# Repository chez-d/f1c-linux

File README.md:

# f1c-linux
This is a little breakout I made for Allwinner's F1C100s/200s a while ago, also known as the "potatoboard" (it's a 533 MHz ARM9 CPU).

This chip is pretty amazing in terms of cost -- for a couple of $$ you can get really impressive performance, at least if you ignore floating point, and up to 64 MB (!!) of DDR as SiP, so no annoying routing to be seen. This board is designed for JLC's low-cost 4 layer boards and you can even get it assembled by them for pretty cheap, go check out the `fab/` folder for the gerbers and POS files!

I used LDOs on this design so I don't have to deal with switching regulator headaches... so not so great power usage.

Upload to the SPI NOR with the USB connector and the handy `sunxi-fel` tool, or you could try and hook up a SD/MMC card on the GPIO. It even runs Linux!

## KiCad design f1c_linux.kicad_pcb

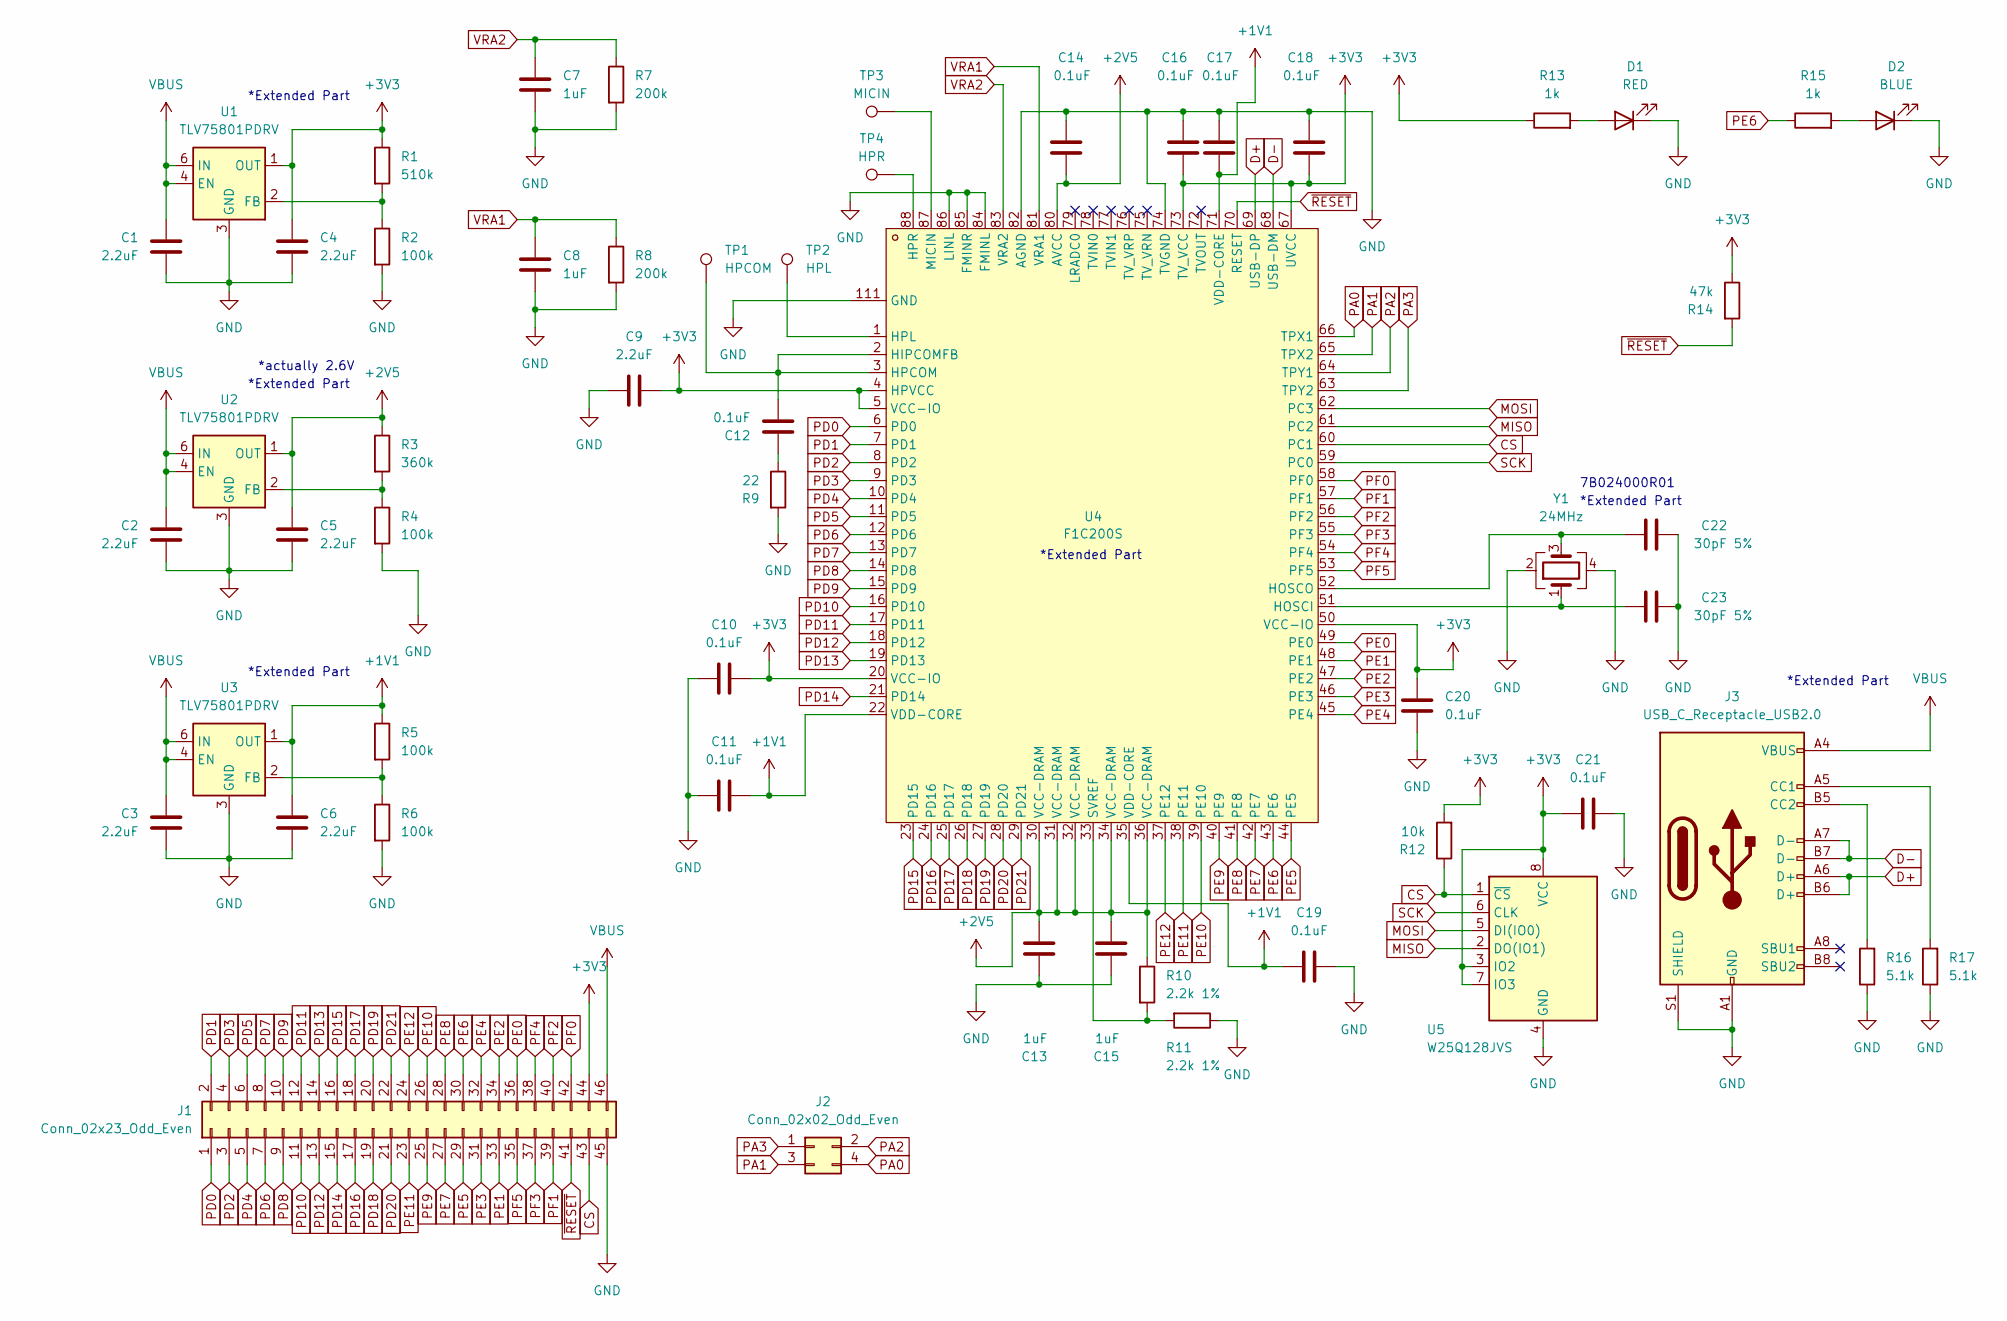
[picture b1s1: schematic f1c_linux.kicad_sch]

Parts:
C1, C2, C3, C4, C5, C6, C9: 2.2uF; C_0603_1608Metric; LCSC Part C23630
C7, C8, C13, C15: 1uF; C_0402_1005Metric; LCSC Part C52923
C10, C11, C12, C14, C16, C17, C18, C19, C20, C21: 0.1uF; C_0402_1005Metric; LCSC Part C307331
C22, C23: 30pF 5%; C_0402_1005Metric; LCSC Part C1570
D1: RED; LED_0603_1608Metric; LCSC Part C2286
D2: BLUE; LED_0603_1608Metric; LCSC Part C72041
J1: Conn_02x23_Odd_Even; PinHeader_2x23_P2.54mm_Vertical
J2: Conn_02x02_Odd_Even; PinHeader_2x02_P2.54mm_Vertical
J3: USB_C_Receptacle_USB2.0; USB_C_Receptacle_G-Switch_GT-USB-7010ASV; LCSC Part C2988369
R1: 510k; R_0402_1005Metric; LCSC Part C11616
R2, R4, R5, R6: 100k; R_0402_1005Metric; LCSC Part C25741
R3: 360k; R_0603_1608Metric; LCSC Part C23146
R7, R8: 200k; R_0402_1005Metric; LCSC Part C25764
R9: 22; R_0402_1005Metric; LCSC Part C25092
R10, R11: 2.2k 1%; R_0402_1005Metric; LCSC Part C25879
R12: 10k; R_0402_1005Metric; LCSC Part C25744
R13, R15: 1k; R_0402_1005Metric; LCSC Part C11702
R14: 47k; R_0402_1005Metric; LCSC Part C25792
R16, R17: 5.1k; R_0402_1005Metric; LCSC Part C25905
TP1: HPCOM; TestPoint_Pad_D2.0mm
TP2: HPL; TestPoint_Pad_D2.0mm
TP3: MICIN; TestPoint_Pad_D2.0mm
TP4: HPR; TestPoint_Pad_D2.0mm
U1, U2, U3: TLV75801PDRV; WSON-6-1EP_2x2mm_P0.65mm_EP1x1.6mm; LCSC Part C2876308
U4: F1C200S; QFN-88_L10.0-W10.0-P0.40-BL-EP6.75; LCSC Part C2879851
U5: W25Q128JVS; SOIC-8_5.23x5.23mm_P1.27mm; LCSC Part C97521
Y1: 24MHz; Crystal_SMD_3225-4Pin_3.2x2.5mm; LCSC Part C654992

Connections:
+1V1: C6.1, C11.2, C17.1, C19.1, R5.1, U3.1 (OUT), U4.22 (VDD-CORE), U4.35 (VDD-CORE), U4.71 (VDD-CORE)
+2V5: C5.1, C13.1, C14.1, C15.1, R3.1, R10.1, U2.1 (OUT), U4.30 (VCC-DRAM), U4.31 (VCC-DRAM), U4.32 (VCC-DRAM), U4.34 (VCC-DRAM), U4.36 (VCC-DRAM), U4.80 (AVCC)
+3V3: C4.1, C9.2, C10.2, C16.1, C18.1, C20.2, C21.2, J1.44, R1.1, R12.2, R13.1, R14.1, U1.1 (OUT), U4.4 (HPVCC), U4.5 (VCC-IO), U4.20 (VCC-IO), U4.50 (VCC-IO), U4.67 (UVCC), U4.73 (TV_VCC), U5.3 (IO2), U5.7 (IO3), U5.8 (VCC)
CS: J1.43, R12.1, U4.60 (PC1), U5.1 (~CS)
D+: J3.A6 (D+), J3.B6 (D+), U4.69 (USB-DP)
D-: J3.A7 (D-), J3.B7 (D-), U4.68 (USB-DM)
GND: C1.2, C2.2, C3.2, C4.2, C5.2, C6.2, C7.2, C8.2, C9.1, C10.1, C11.1, C13.2, C14.2, C15.2, C16.2, C17.2, C18.2, C19.2, C20.1, C21.1, C22.2, C23.2, D1.1 (K), D2.1 (K), J1.45, J3.A1 (GND), J3.A12 (GND), J3.B1 (GND), J3.B12 (GND), J3.S1 (SHIELD), R2.2, R4.2, R6.2, R7.2, R8.2, R9.2, R11.1, R16.1, R17.1, U1.3 (GND), U1.7 (GND), U2.3 (GND), U2.7 (GND), U3.3 (GND), U3.7 (GND), U4.74 (TVGND), U4.82 (AGND), U4.84 (FMINL), U4.85 (FMINR), U4.86 (LINL), U4.111 (GND), U5.4 (GND), Y1.2, Y1.4
MISO: U4.61 (PC2), U5.2 (DO(IO1))
MOSI: U4.62 (PC3), U5.5 (DI(IO0))
unnamed: C12.1, R9.1
unnamed: D1.2 (A), R13.2
unnamed: D2.2 (A), R15.2
unnamed: J3.A5 (CC1), R17.2
unnamed: J3.B5 (CC2), R16.2
unnamed: R1.2, R2.1, U1.2 (FB)
unnamed: R3.2, R4.1, U2.2 (FB)
unnamed: R5.2, R6.1, U3.2 (FB)
unnamed: C12.2, TP1.1, U4.2 (HIPCOMFB), U4.3 (HPCOM)
unnamed: C23.1, U4.51 (HOSCI), Y1.1
unnamed: C22.1, U4.52 (HOSCO), Y1.3
unnamed: TP2.1, U4.1 (HPL)
unnamed: TP4.1, U4.88 (HPR)
unnamed: TP3.1, U4.87 (MICIN)
unnamed: R10.2, R11.2, U4.33 (SVREF)
PA0: J2.4, U4.66 (TPX1)
PA1: J2.3, U4.65 (TPX2)
PA2: J2.2, U4.64 (TPY1)
PA3: J2.1, U4.63 (TPY2)
PD0: J1.1, U4.6 (PD0)
PD1: J1.2, U4.7 (PD1)
PD2: J1.3, U4.8 (PD2)
PD3: J1.4, U4.9 (PD3)
PD4: J1.5, U4.10 (PD4)
PD5: J1.6, U4.11 (PD5)
PD6: J1.7, U4.12 (PD6)
PD7: J1.8, U4.13 (PD7)
PD8: J1.9, U4.14 (PD8)
PD9: J1.10, U4.15 (PD9)
PD10: J1.11, U4.16 (PD10)
PD11: J1.12, U4.17 (PD11)
PD12: J1.13, U4.18 (PD12)
PD13: J1.14, U4.19 (PD13)
PD14: J1.15, U4.21 (PD14)
PD15: J1.16, U4.23 (PD15)
PD16: J1.17, U4.24 (PD16)
PD17: J1.18, U4.25 (PD17)
PD18: J1.19, U4.26 (PD18)
PD19: J1.20, U4.27 (PD19)
PD20: J1.21, U4.28 (PD20)
PD21: J1.22, U4.29 (PD21)
PE0: J1.36, U4.49 (PE0)
PE1: J1.33, U4.48 (PE1)
PE2: J1.34, U4.47 (PE2)
PE3: J1.31, U4.46 (PE3)
PE4: J1.32, U4.45 (PE4)
PE5: J1.29, U4.44 (PE5)
PE6: J1.30, R15.1, U4.43 (PE6)
PE7: J1.27, U4.42 (PE7)
PE8: J1.28, U4.41 (PE8)
PE9: J1.25, U4.40 (PE9)
PE10: J1.26, U4.39 (PE10)
PE11: J1.23, U4.38 (PE11)
PE12: J1.24, U4.37 (PE12)
PF0: J1.42, U4.58 (PF0)
PF1: J1.39, U4.57 (PF1)
PF2: J1.40, U4.56 (PF2)
PF3: J1.37, U4.55 (PF3)
PF4: J1.38, U4.54 (PF4)
PF5: J1.35, U4.53 (PF5)
SCK: U4.59 (PC0), U5.6 (CLK)
VBUS: C1.1, C2.1, C3.1, J1.46, J3.A4 (VBUS), J3.A9 (VBUS), J3.B4 (VBUS), J3.B9 (VBUS), U1.4 (EN), U1.6 (IN), U2.4 (EN), U2.6 (IN), U3.4 (EN), U3.6 (IN)
VRA1: C8.1, R8.1, U4.81 (VRA1)
VRA2: C7.1, R7.1, U4.83 (VRA2)
~RESET: J1.41, R14.2, U4.70 (RESET)

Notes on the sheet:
*Extended Part
7B024000R01
*actually 2.6V

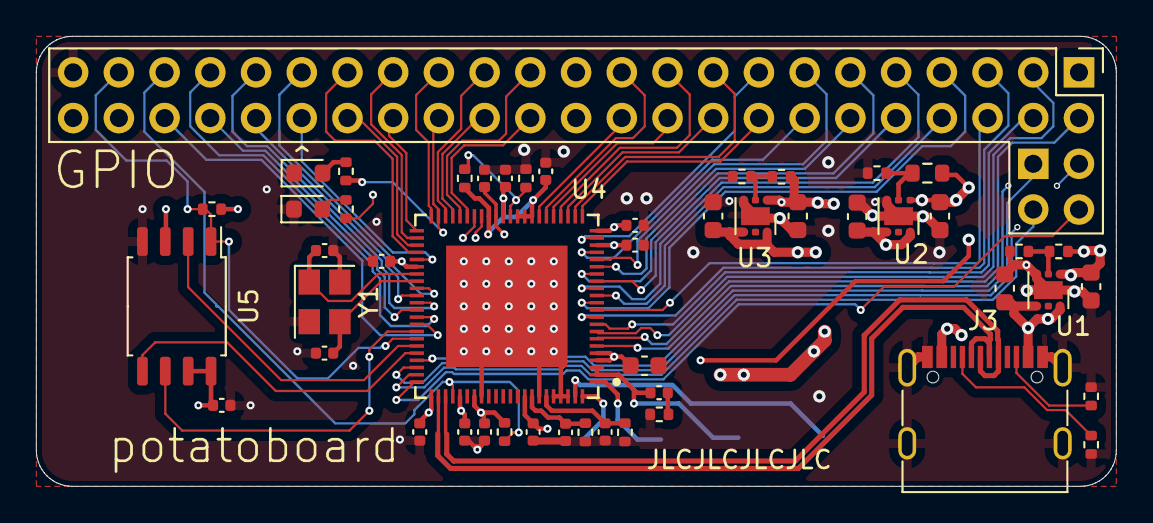
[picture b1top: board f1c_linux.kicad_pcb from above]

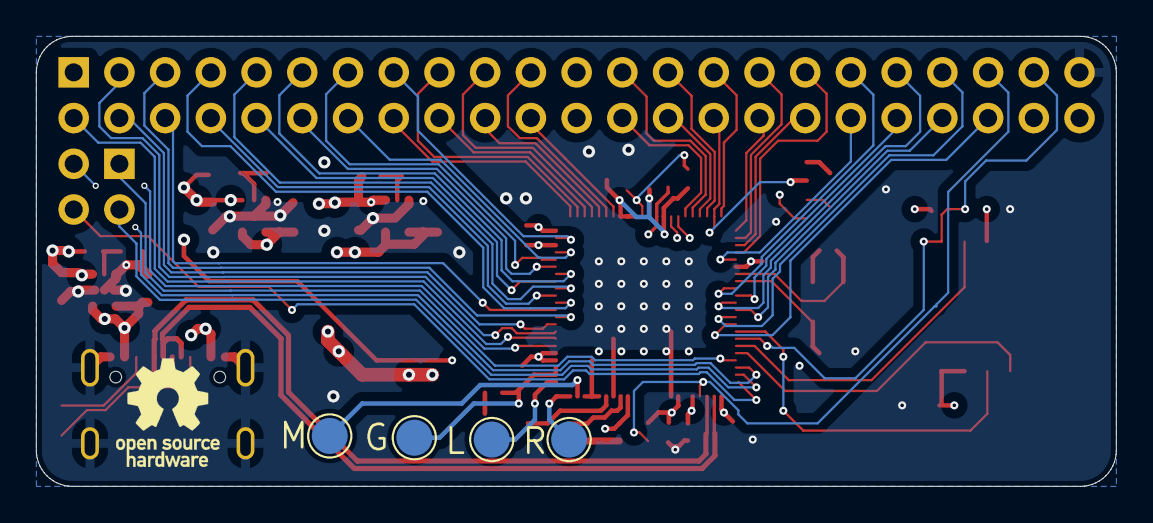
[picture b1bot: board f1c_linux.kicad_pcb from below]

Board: 4 copper layers, 60.0 x 25.0 mm, 55 parts (4 on the bottom side), 74 nets.

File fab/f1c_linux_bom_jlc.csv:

"Comment","Designator","Footprint","LCSC Part Number"
"2.2uF","C1,C2,C3,C4,C5,C6,C9","C_0603_1608Metric","C23630"
"1uF","C7,C8,C13,C15","C_0402_1005Metric","C52923"
"0.1uF","C10,C11,C12,C14,C16,C17,C18,C19,C20,C21","C_0402_1005Metric","C307331"
"30pF 5%","C22,C23","C_0402_1005Metric","C1570"
"RED","D1","LED_0603_1608Metric","C2286"
"BLUE","D2","LED_0603_1608Metric","C72041"
"USB_C_Receptacle_USB2.0","J3","USB_C_Receptacle_G-Switch_GT-USB-7010ASV","C2988369"
"510k","R1","R_0402_1005Metric","C11616"
"100k","R2,R4,R5,R6","R_0402_1005Metric","C25741"
"360k","R3","R_0603_1608Metric","C23146"
"200k","R7,R8","R_0402_1005Metric","C25764"
"22","R9","R_0402_1005Metric","C25092"
"2.2k 1%","R10,R11","R_0402_1005Metric","C25879"
"10k","R12","R_0402_1005Metric","C25744"
"1k","R13,R15","R_0402_1005Metric","C11702"
"47k","R14","R_0402_1005Metric","C25792"
"5.1k","R16,R17","R_0402_1005Metric","C25905"
"TLV75801PDRV","U1,U2,U3","WSON-6-1EP_2x2mm_P0.65mm_EP1x1.6mm","C2876308"
"F1C200S","U4","QFN-88_L10.0-W10.0-P0.40-BL-EP6.75","C2879851"
"W25Q128JVS","U5","SOIC-8_5.23x5.23mm_P1.27mm","C97521"
"24MHz","Y1","Crystal_SMD_3225-4Pin_3.2x2.5mm","C654992"

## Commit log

2024-03-28 Write README
